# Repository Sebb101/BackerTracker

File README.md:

# BackerTracker
Tracker for HPR applications

STM32 MCU

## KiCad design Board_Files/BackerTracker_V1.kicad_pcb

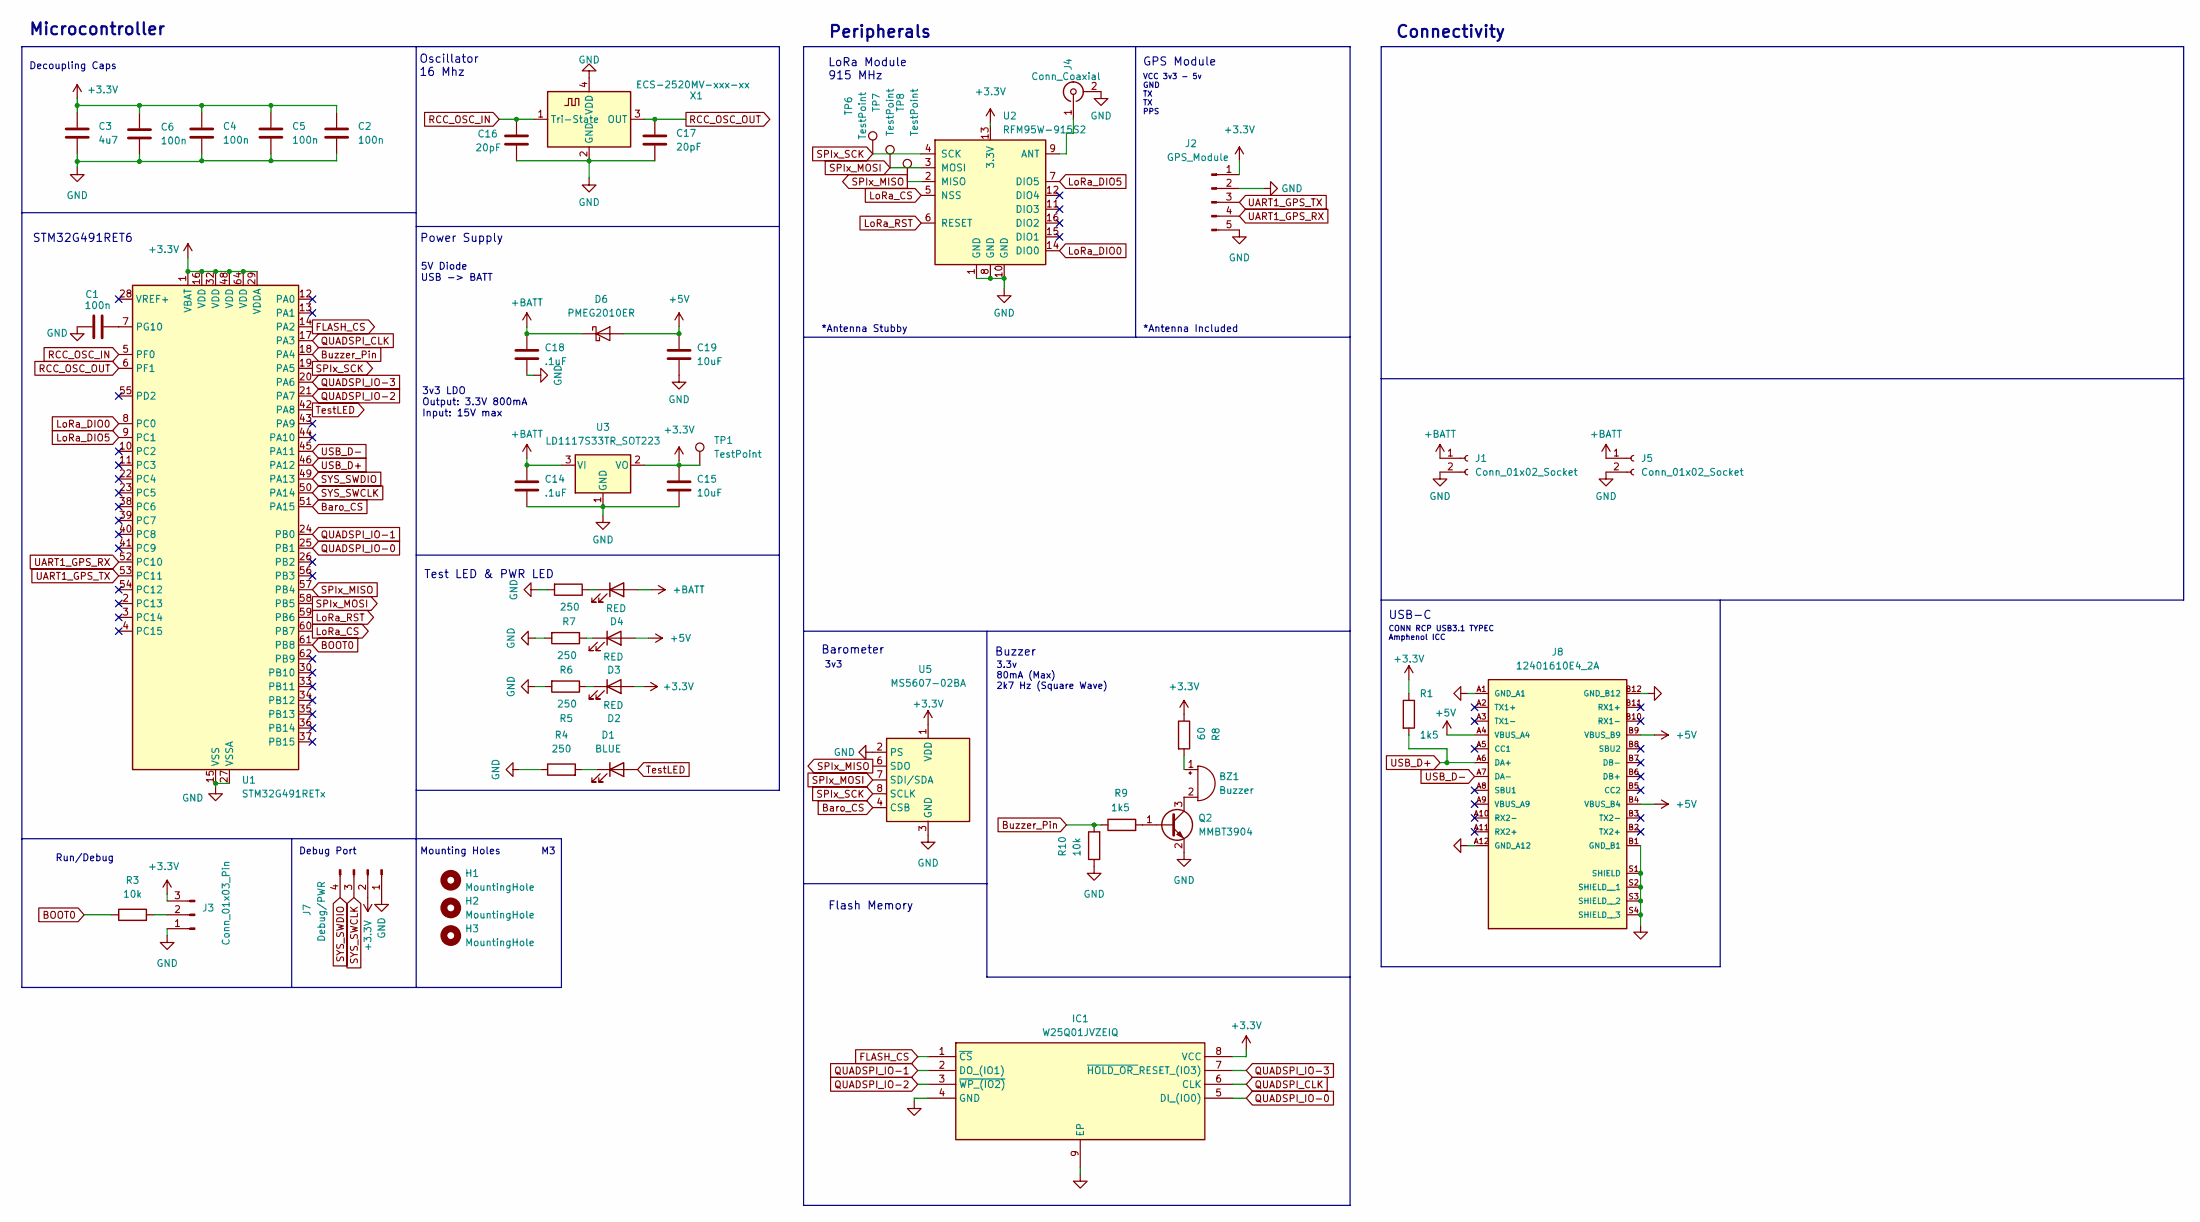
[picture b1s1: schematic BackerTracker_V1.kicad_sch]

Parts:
BZ1: Buzzer; SMTB-0927-TW-R_PUI
C1, C2, C4, C5, C6: 100n; C_0402_1005Metric
C3: 4u7; C_0402_1005Metric
C14, C18: .1uF; C_0402_1005Metric
C15, C19: 10uF; C_0603_1608Metric
C16, C17: 20pF; C_0402_1005Metric
D1: BLUE; LED_0603_1608Metric
D2, D3, D4: RED; LED_0603_1608Metric
D6: PMEG2010ER; Nexperia_CFP3_SOD-123W
H1, H2, H3: MountingHole; MountingHole_3.2mm_M3
IC1: W25Q01JVZEIQ; WSON-8-1EP_8x6mm_P1.27mm_EP3.4x4.3mm; Mouser Part Number 454-W25Q01JVZEIQ
J1: Conn_01x02_Socket; JST_PH_S2B-PH-K_1x02_P2.00mm_Horizontal
J2: GPS_Module; ATGM336H_GPS
J3: Conn_01x03_Pin; PinHeader_1x03_P2.54mm_Vertical
J4: Conn_Coaxial; SMA_Samtec_SMA-J-P-H-ST-EM1_EdgeMount
J5: Conn_01x02_Socket; PinHeader_1x02_P2.54mm_Vertical
J7: Debug/PWR; PinHeader_1x04_P2.54mm_Vertical
J8: 12401610E4_2A; AMPHENOL_12401598E4_2A; PARTREV C
Q2: MMBT3904; SOT-23
R1, R9: 1k5; R_0402_1005Metric
R3, R10: 10k; R_0402_1005Metric
R4, R5, R6, R7: 250; R_0402_1005Metric
R8: 60; R_0402_1005Metric
TP1, TP6, TP7, TP8: TestPoint; TestPoint_Keystone_5005-5009_Compact
U1: STM32G491RETx; LQFP-64_10x10mm_P0.5mm
U2: RFM95W-915S2; HOPERF_RFM9XW_SMD
U3: LD1117S33TR_SOT223; SOT-223-3_TabPin2
U5: MS5607-02BA; LGA-8_3x5mm_P1.25mm
X1: ECS-2520MV-xxx-xx; Oscillator_SMD_ECS_2520MV-xxx-xx-4Pin_2.5x2.0mm

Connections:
+3.3V: C2.1, C3.1, C4.1, C5.1, C6.1, C15.1, D2.2 (A), IC1.8 (VCC), J2.1, J3.3, J7.2, R1.1, R8.1, TP1.1, U1.1 (VBAT), U1.16 (VDD), U1.29 (VDDA), U1.32 (VDD), U1.48 (VDD), U1.64 (VDD), U2.13 (3.3V), U3.2 (VO), U5.1 (VDD)
+5V: C19.1, D3.2 (A), D6.2 (A), J8.A4 (VBUS_A4), J8.B4 (VBUS_B4), J8.B9 (VBUS_B9)
+BATT: C14.1, C18.1, D4.2 (A), D6.1 (K), J1.1, J5.1, U3.3 (VI)
BOOT0: R3.1, U1.61 (PB8)
Baro_CS: U1.51 (PA15), U5.4 (CSB), U5.5 (CSB)
Buzzer_Pin: R9.1, R10.2, U1.18 (PA4)
FLASH_CS: IC1.1 (~CS), U1.14 (PA2)
GND: C1.2, C2.2, C3.2, C4.2, C5.2, C6.2, C14.2, C15.2, C16.2, C17.2, C18.2, C19.2, IC1.4 (GND), IC1.9 (EP), J1.2, J2.2, J2.5, J3.1, J4.2 (Ext), J5.2, J7.1, J8.A1 (GND_A1), J8.A12 (GND_A12), J8.B1 (GND_B1), J8.B12 (GND_B12), J8.S1 (SHIELD), J8.S2 (SHIELD__1), J8.S3 (SHIELD__2), J8.S4 (SHIELD__3), Q2.2 (E), R4.1, R5.2, R6.2, R7.2, R10.1, U1.15 (VSS), U1.27 (VSSA), U1.31 (VSS), U1.47 (VSS), U1.63 (VSS), U2.1 (GND), U2.8 (GND), U2.10 (GND), U3.1 (GND), U5.2 (PS), U5.3 (GND), X1.2 (GND), X1.4 (VDD)
LoRa_CS: U1.60 (PB7), U2.5 (NSS)
LoRa_DIO0: U1.8 (PC0), U2.14 (DIO0)
LoRa_DIO5: U1.9 (PC1), U2.7 (DIO5)
LoRa_RST: U1.59 (PB6), U2.6 (RESET)
unnamed: BZ1.1 (+), R8.2
unnamed: BZ1.2 (-), Q2.3 (C)
unnamed: D1.1 (K), R4.2
unnamed: D2.1 (K), R5.1
unnamed: D3.1 (K), R6.1
unnamed: D4.1 (K), R7.1
unnamed: J3.2, R3.2
unnamed: J4.1 (In), U2.9 (ANT)
unnamed: Q2.1 (B), R9.2
unnamed: C1.1, U1.7 (PG10)
QUADSPI_CLK: IC1.6 (CLK), U1.17 (PA3)
QUADSPI_IO-0: IC1.5 (DI_(IO0)), U1.25 (PB1)
QUADSPI_IO-1: IC1.2 (DO_(IO1)), U1.24 (PB0)
QUADSPI_IO-2: IC1.3 (~WP_(IO2)), U1.21 (PA7)
QUADSPI_IO-3: IC1.7 (~HOLD_OR_RESET_(IO3)), U1.20 (PA6)
RCC_OSC_IN: C16.1, U1.5 (PF0), X1.1 (Tri-State)
RCC_OSC_OUT: C17.1, U1.6 (PF1), X1.3 (OUT)
SPIx_MISO: TP8.1, U1.57 (PB4), U2.2 (MISO), U5.6 (SDO)
SPIx_MOSI: TP7.1, U1.58 (PB5), U2.3 (MOSI), U5.7 (SDI/SDA)
SPIx_SCK: TP6.1, U1.19 (PA5), U2.4 (SCK), U5.8 (SCLK)
SYS_SWCLK: J7.3, U1.50 (PA14)
SYS_SWDIO: J7.4, U1.49 (PA13)
TestLED: D1.2 (A), U1.42 (PA8)
UART1_GPS_RX: J2.4, U1.52 (PC10)
UART1_GPS_TX: J2.3, U1.53 (PC11)
USB_D+: J8.A6 (DA+), R1.2, U1.46 (PA12)
USB_D-: J8.A7 (DA-), U1.45 (PA11)

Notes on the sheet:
Mounting Holes
Flash Memory
LoRa Module 915 MHz
Connectivity
Buzzer
3v3 LDO Output: 3.3V 800mA Input: 15V max
Power Supply
GPS Module
Decoupling Caps
Run/Debug
*Antenna Stubby
STM32G491RET6
Test LED & PWR LED
Debug Port
*Antenna Included
5V Diode USB -> BATT
Oscillator 16 Mhz
Peripherals
3v3
CONN RCP USB3.1 TYPEC Amphenol ICC
USB-C
VCC 3v3 - 5v GND TX TX PPS
3.3v 80mA (Max) 2k7 Hz (Square Wave)
Microcontroller
Barometer

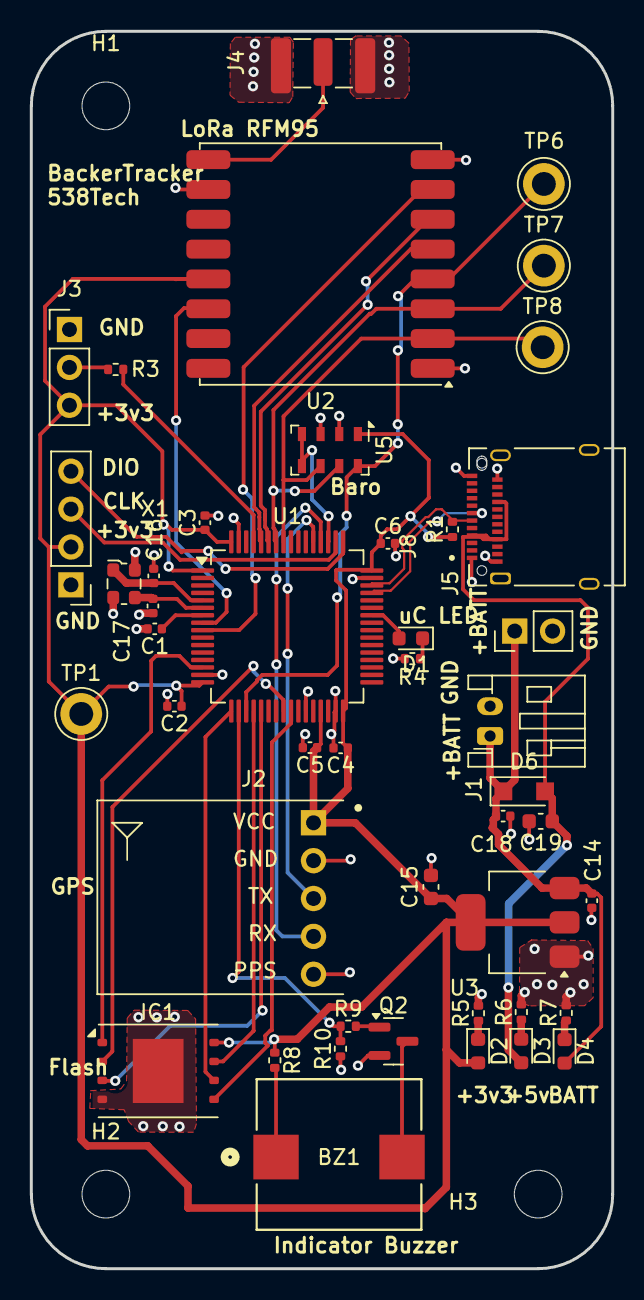
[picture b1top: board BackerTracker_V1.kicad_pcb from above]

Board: 2 copper layers, 39.0 x 83.0 mm, 48 parts (0 on the bottom side), 39 nets.

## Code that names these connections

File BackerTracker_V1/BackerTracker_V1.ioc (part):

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Mcu.Name=STM32G491R(C-E)Tx
Mcu.Package=LQFP64
Mcu.UserName=STM32G491RETx
PA11.Mode=Device
PA11.Signal=USB_DM
PA12.Mode=Device
PA12.Signal=USB_DP
PA13.Mode=Serial_Wire
PA13.Signal=SYS_JTMS-SWDIO
PA14.Mode=Serial_Wire
PA14.Signal=SYS_JTCK-SWCLK
PA15.Signal=GPIO_Output
PA2.Mode=Single Bank 1
PA2.Signal=QUADSPI1_BK1_NCS
PA3.Mode=Single Bank 1
PA3.Signal=QUADSPI1_CLK
PA4.Signal=S_TIM3_CH2
PA5.Mode=Full_Duplex_Master
PA5.Signal=SPI1_SCK
PA6.Mode=Single Bank 1
PA6.Signal=QUADSPI1_BK1_IO3
PA7.Mode=Single Bank 1
PA7.Signal=QUADSPI1_BK1_IO2
PA8.Signal=GPIO_Output
PB0.Mode=Single Bank 1
PB0.Signal=QUADSPI1_BK1_IO1
PB1.Mode=Single Bank 1
PB1.Signal=QUADSPI1_BK1_IO0
PB11.Signal=GPIO_Output
PB12.Signal=GPIO_Output
PB13.Signal=GPIO_Output
PB14.Signal=GPIO_Output
PB3.Signal=GPIO_Output
PB4.Mode=Full_Duplex_Master
PB4.Signal=SPI1_MISO
PB5.Mode=Full_Duplex_Master
PB5.Signal=SPI1_MOSI
PB6.Signal=GPIO_Output
PB7.Signal=GPIO_Output
PC0.Signal=GPXTI0
PC1.Signal=GPXTI1
PC10.Mode=Asynchronous
PC10.Signal=UART4_TX
PC11.Mode=Asynchronous
PC11.Signal=UART4_RX
PC12.Signal=GPIO_Output
PC2.Signal=GPXTI2
PC3.Signal=GPXTI3
PC4.Signal=GPXTI4
PC5.Signal=GPXTI5
PD2.Signal=GPIO_Output
PF0-OSC_IN.Mode=HSE-External-Oscillator
PF0-OSC_IN.Signal=RCC_OSC_IN
PF1-OSC_OUT.Mode=HSE-External-Oscillator
PF1-OSC_OUT.Signal=RCC_OSC_OUT
RCC.HSE_VALUE=16000000
RCC.SYSCLKFreq_VALUE=16000000
board=custom

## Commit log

2025-07-19 Latest firmware for project
2025-07-20 Promdata all 7710 error
